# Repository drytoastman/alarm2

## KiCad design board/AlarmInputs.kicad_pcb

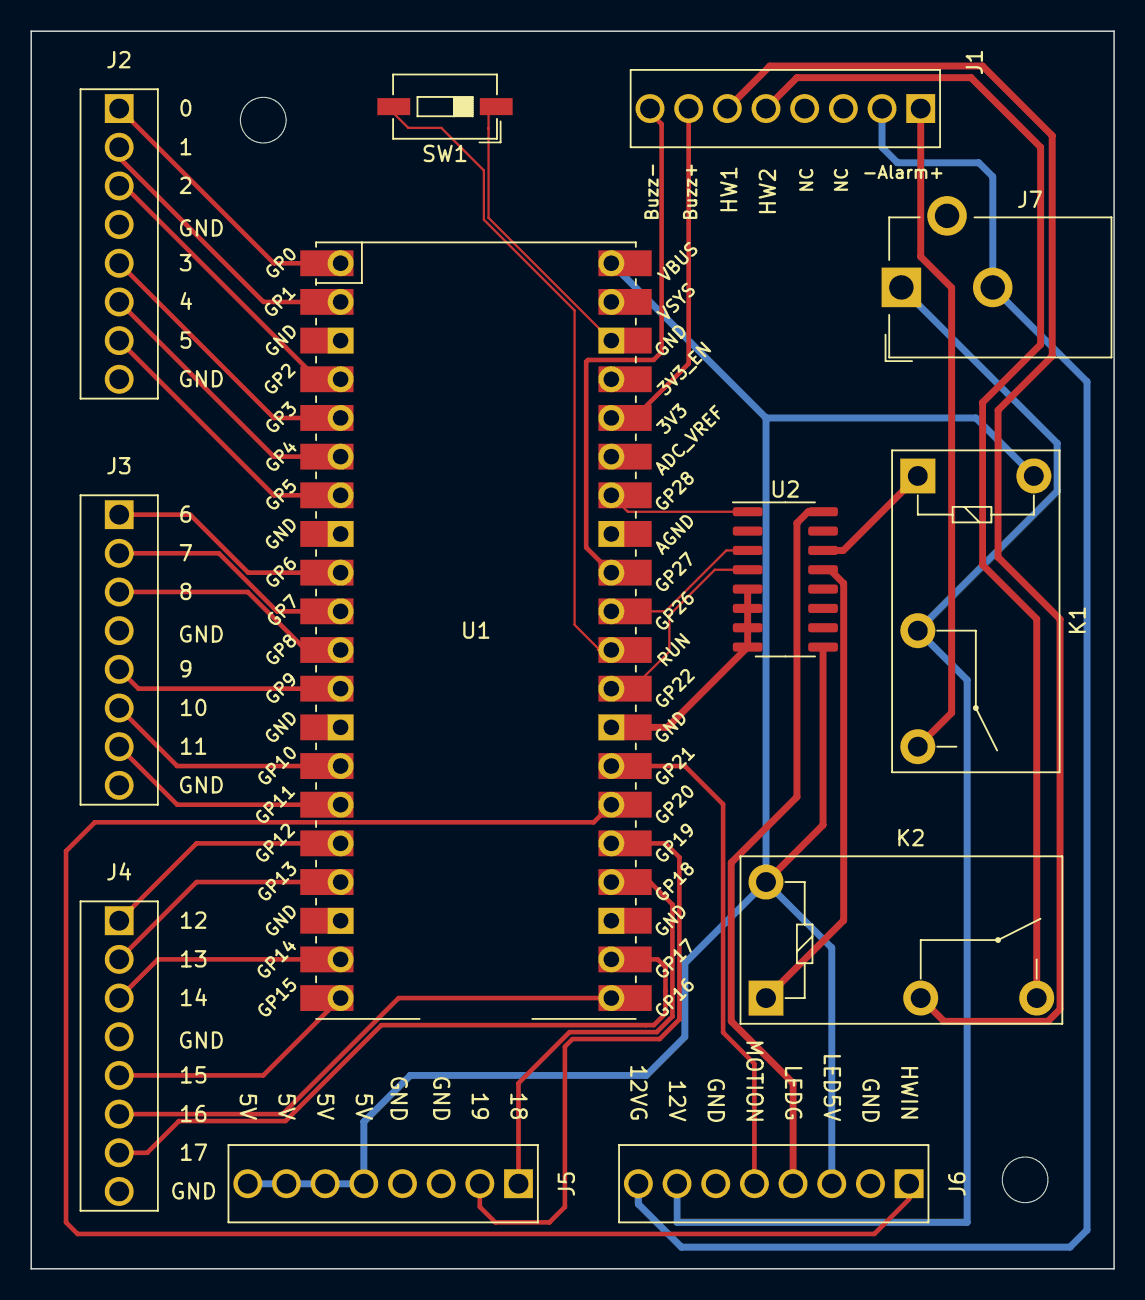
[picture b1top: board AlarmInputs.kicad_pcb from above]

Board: 2 copper layers, 71.1 x 81.3 mm, 14 parts (0 on the bottom side), 38 nets.

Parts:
H1, H2: MountingHole; MountingHole_3mm
J1: External Devices; 8pinscrew
J2, J3, J4, J5: Inputs; 8pinscrew
J6: 4-Wire Connections; 8pinscrew
J7: Barrel_Jack_Switch; BarrelJack_CUI_PJ-102AH_Horizontal
K1, K2: G5Q-1A; Relay_SPST_Omron-G5Q-1A
SW1: Reset; SW_DIP_SPSTx01_Slide_6.7x4.1mm_W6.73mm_P2.54mm_LowProfile_J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
U1: Pico; RPi_Pico_SMD_TH
U2: ULN2003; SOIC-16_3.9x9.9mm_P1.27mm

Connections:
3.3V: J1.7, U1.36
5V: J5.5, J5.6, J5.7, J5.8, J6.3, K1.5, K2.5, U1.40, U2.9
12V: J6.7, J7.1, K1.2
12VGND: J1.2, J6.8, J7.2
ALARM: J1.1, K1.3
BUZZERGND: J1.8, U1.32
GND: J2.4, J2.8, J3.4, J3.8, J4.4, J4.8, J5.3, J5.4, J6.2, J6.6, SW1.1, U1.3, U1.8, U1.13, U1.18, U1.23, U1.28, U1.33, U1.38, U2.5, U2.6, U2.7, U2.8
HW1: J1.6, K2.2
HW2: J1.5, K2.3
HWINPUT: J6.1, U1.26
IO0: J2.1, U1.1
IO1: J2.2, U1.2
IO2: J2.3, U1.4
IO3: J2.5, U1.5
IO4: J2.6, U1.6
IO5: J2.7, U1.7
IO6: J3.1, U1.9
IO7: J3.2, U1.10
IO8: J3.3, U1.11
IO9: J3.5, U1.12
IO10: J3.6, U1.14
IO11: J3.7, U1.15
IO12: J4.1, U1.16
IO13: J4.2, U1.17
IO14: J4.3, U1.19
IO15: J4.5, U1.20
IO16: J4.6, U1.21
IO17: J4.7, U1.22
IO18: J5.1, U1.24
IO19: J5.2, U1.25
LEDGND: J6.4, U2.16
MOTION: J6.5, U1.27
unnamed: K1.1, U2.14
unnamed: K2.1, U2.13
unnamed: U1.29, U2.4
unnamed: U1.31, U2.3
unnamed: U1.34, U2.1
RST: SW1.2, U1.30

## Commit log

2021-08-01 copy/paste/search/replace and then do other things for the initial files
2021-08-01 flush out directories
2021-08-01 add in the kicad board
2021-08-02 split and inputs/outputs, still no hardware to test and no serial processing
2021-08-02 some command processing
2021-08-10 make path relative for moving around
2021-09-22 fix blink timeout and newlines
2021-09-22 add sdk as submodule so we can track version
2021-09-27 ignore vscode 'settings'
2021-09-27 fix usb buffering, proper wait and send for tx
2021-09-27 buzzer fix, input initial state and some time fixes
2021-09-27 add option to change a pin debounce online
2021-09-27 direct buzzer connection as darlington pair slews out the square wave too much
2021-10-11 update for our outputs, using characters and non-binary values for buzzer/tone and led brightness
2021-10-14 hwled work, pulse when pump is appox active
2021-10-14 get reported value for inputs for initial send
2021-10-14 don't let another hw request happen if currently in one, sleep definitely caused an issue
2022-02-26 read/save options to flash, adjust to our new outputs
2022-02-26 fix output values
2022-02-26 once more
2022-02-27 need to do full setup for led brightness on startup
2022-02-28 still forget which was which
2022-03-08 connect hwswitch to hw_toggle directly
